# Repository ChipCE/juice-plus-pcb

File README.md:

# juice-plus-pcb
Varios PCB design for 3D printers and drones

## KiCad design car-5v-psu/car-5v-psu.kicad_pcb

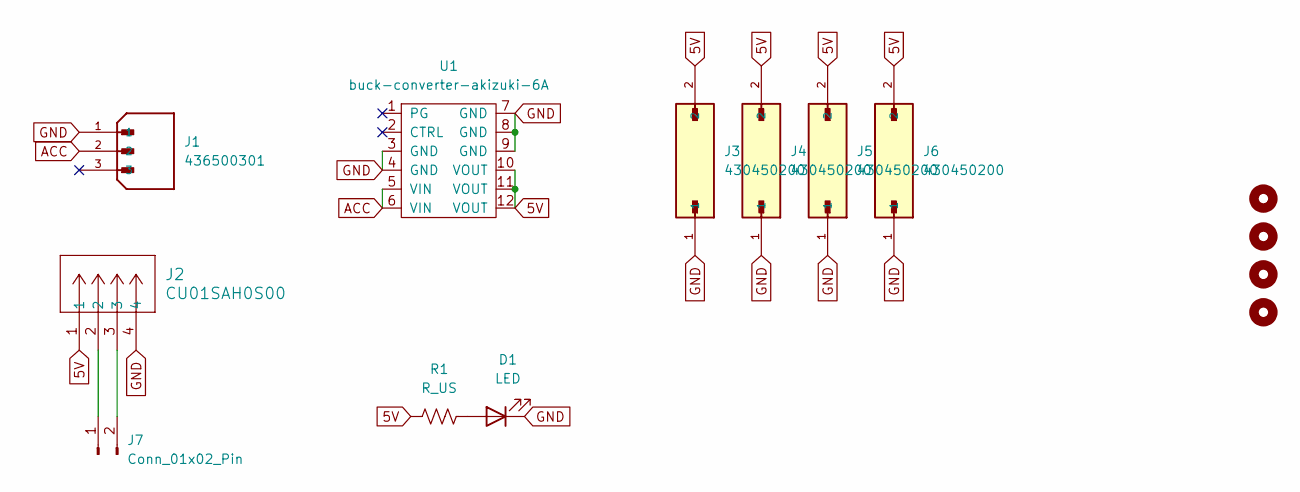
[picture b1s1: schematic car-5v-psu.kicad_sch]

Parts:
D1: LED; LED_0805_2012Metric
H1, H2, H3, H4: MountingHole; MountingHole_3.2mm_M3_ISO7380_Pad
J1: 436500301; MOLEX_436500301; PARTREV D7
J2: CU01SAH0S00; CONN_CU01SAH0S00_CVI
J3, J4, J5, J6: 430450200; MOLEX_430450200; PARTREV G
J7: Conn_01x02_Pin; PinHeader_1x02_P2.54mm_Vertical
R1: R_US; R_0805_2012Metric
U1: buck-converter-akizuki-6A

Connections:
5V: J2.1, J3.2, J4.2, J5.2, J6.2, R1.1, U1.10 (VOUT), U1.11 (VOUT), U1.12 (VOUT)
ACC: J1.2, U1.5 (VIN), U1.6 (VIN)
GND: D1.1 (K), J1.1, J2.4, J3.1, J4.1, J5.1, J6.1, U1.3 (GND), U1.4 (GND), U1.7 (GND), U1.8 (GND), U1.9 (GND)
unnamed: D1.2 (A), R1.2
unnamed: J2.2, J7.1
unnamed: J2.3, J7.2

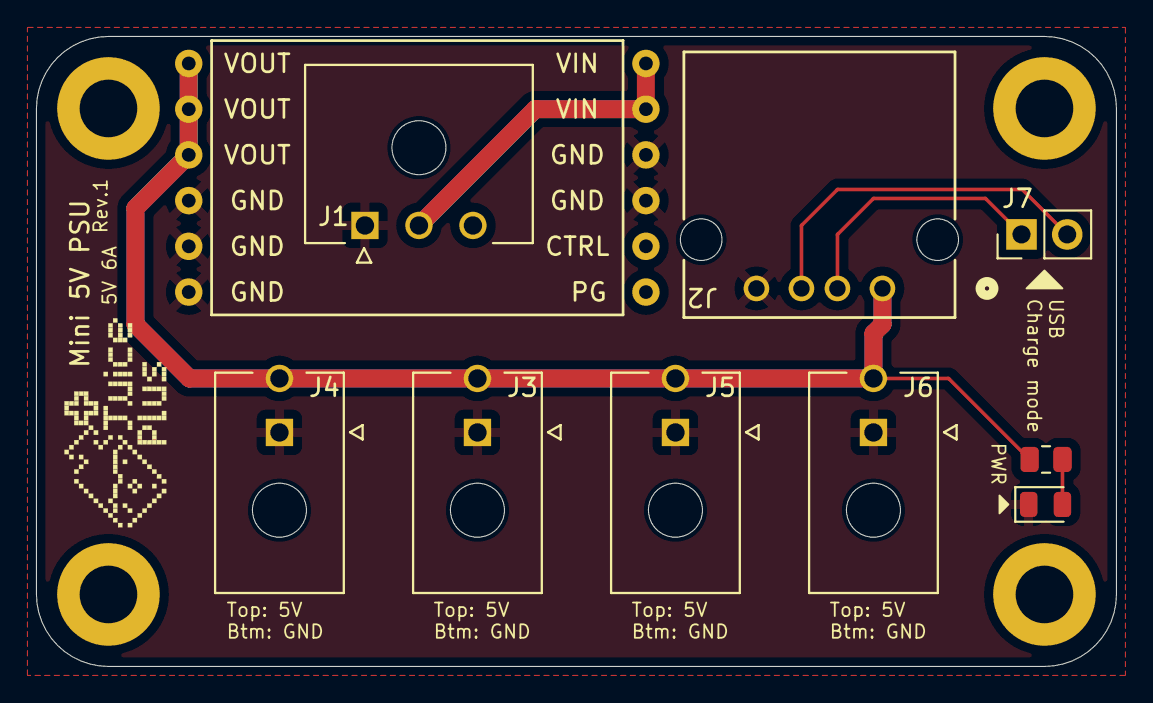
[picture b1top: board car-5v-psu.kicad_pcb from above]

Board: 2 copper layers, 60.0 x 35.0 mm, 14 parts (0 on the bottom side), 6 nets.

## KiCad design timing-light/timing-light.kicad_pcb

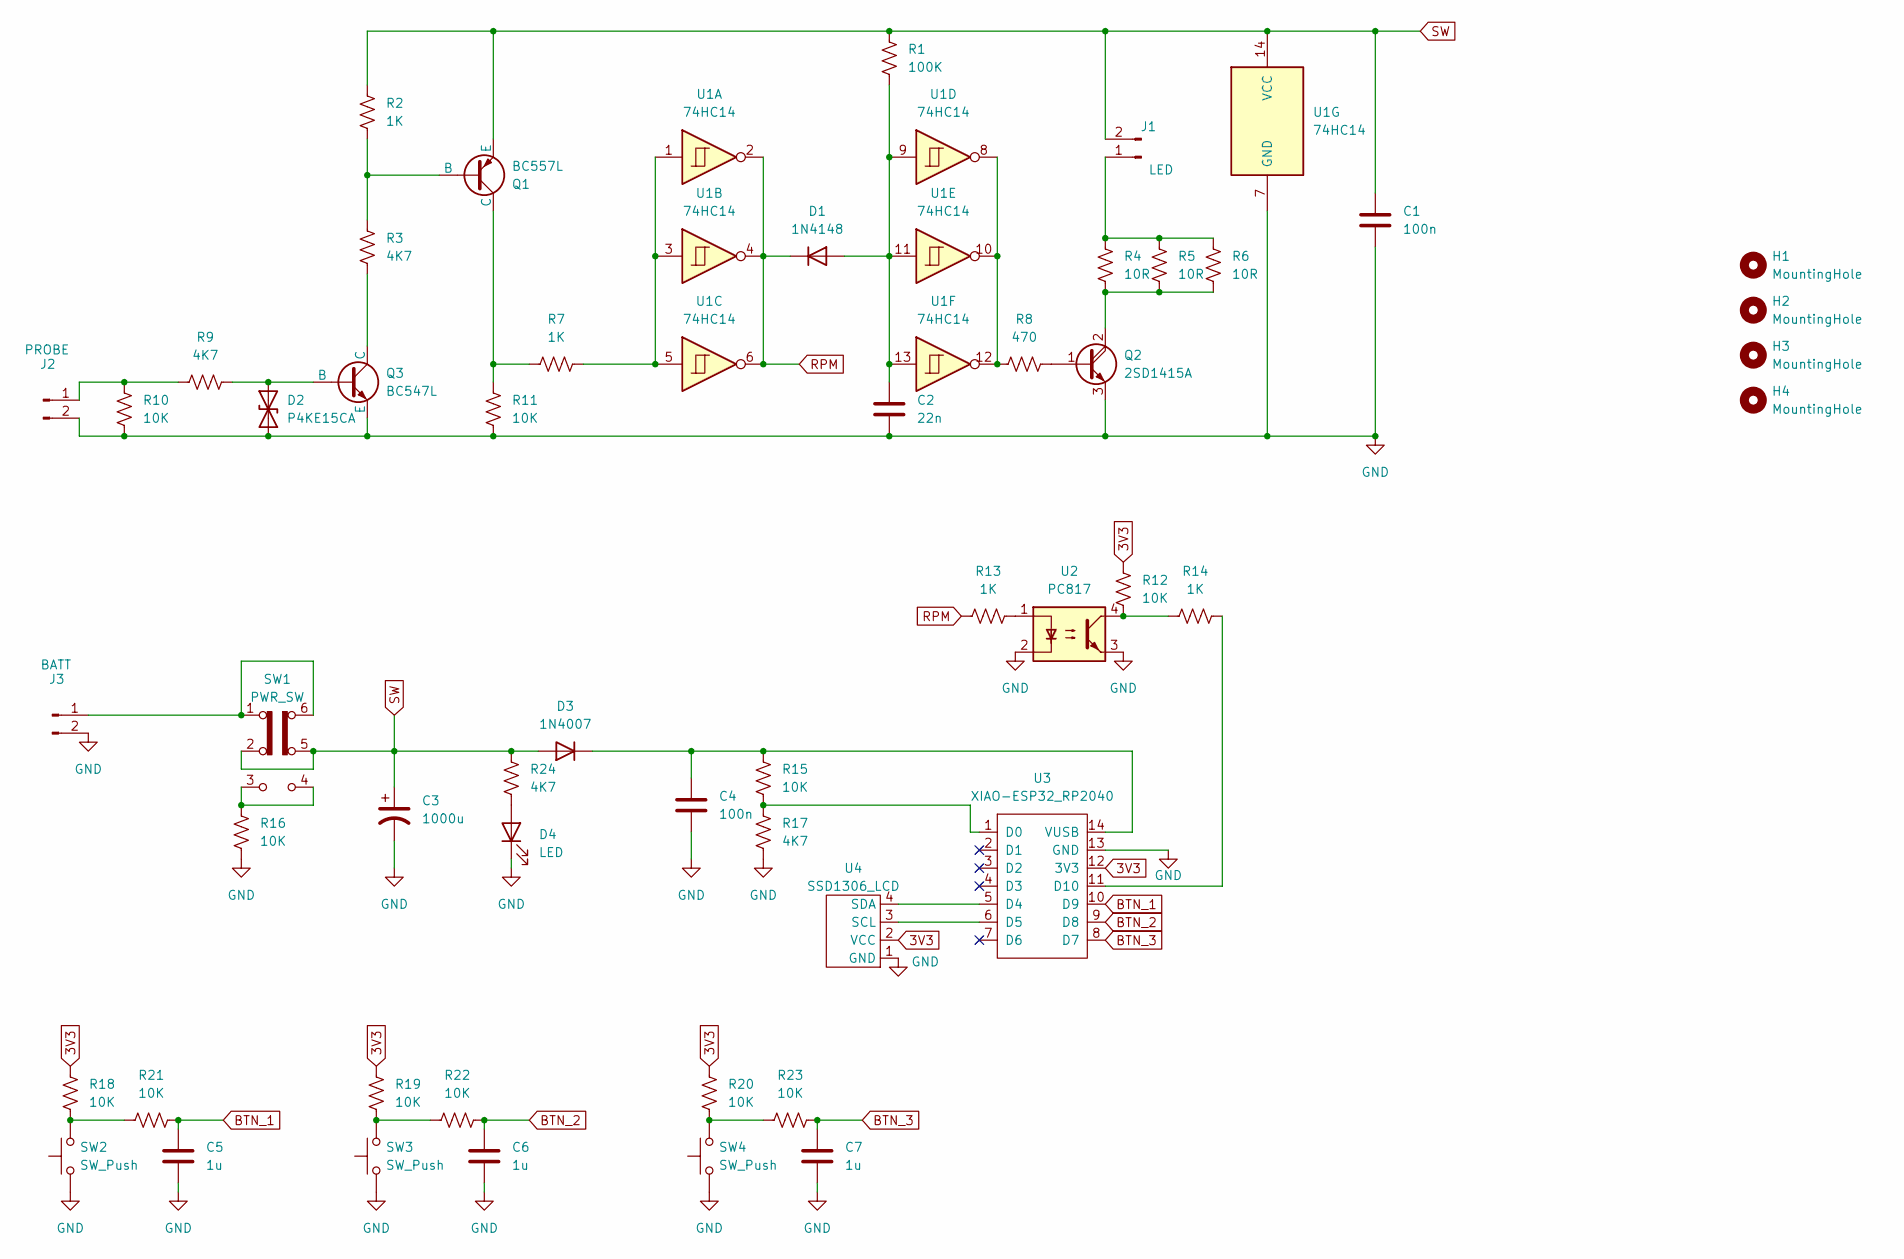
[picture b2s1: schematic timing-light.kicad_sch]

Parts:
C1, C4: 100n; C_Disc_D7.5mm_W4.4mm_P5.00mm
C2: 22n; C_Disc_D14.5mm_W5.0mm_P10.00mm
C3: 1000u; CP_Radial_D10.0mm_P5.00mm
C5, C6, C7: 1u; C_Disc_D7.5mm_W4.4mm_P5.00mm
D1: 1N4148; D_DO-35_SOD27_P7.62mm_Horizontal
D2: P4KE15CA; D_DO-41_SOD81_P10.16mm_Horizontal
D3: 1N4007; D_5W_P10.16mm_Horizontal
D4: LED; LED_D3.0mm_Horizontal_O1.27mm_Z2.0mm
H1, H2, H3, H4: MountingHole; MountingHole_3.2mm_M3_DIN965_Pad
J1: LED; JST_XH_B2B-XH-A_1x02_P2.50mm_Vertical
J2: PROBE; JST_XH_B2B-XH-A_1x02_P2.50mm_Vertical
J3: BATT; JST_XH_B2B-XH-A_1x02_P2.50mm_Vertical
Q1: BC557L; TO-92_Inline
Q2: 2SD1415A; TO-220-3_Horizontal_TabDown
Q3: BC547L; TO-92_Inline
R1: 100K; R_Axial_DIN0207_L6.3mm_D2.5mm_P10.16mm_Horizontal
R2, R7, R13, R14: 1K; R_Axial_DIN0207_L6.3mm_D2.5mm_P10.16mm_Horizontal
R3, R9, R17, R24: 4K7; R_Axial_DIN0207_L6.3mm_D2.5mm_P10.16mm_Horizontal
R4, R5, R6: 10R; R_Axial_DIN0309_L9.0mm_D3.2mm_P12.70mm_Horizontal
R8: 470; R_Axial_DIN0207_L6.3mm_D2.5mm_P10.16mm_Horizontal
R10, R11, R12, R15, R16, R18, R19, R20, R21, R22, R23: 10K; R_Axial_DIN0207_L6.3mm_D2.5mm_P10.16mm_Horizontal
SW1: PWR_SW; Switch_SS22F06G5
SW2, SW3, SW4: SW_Push; SW_PUSH_6mm
U1: 74HC14; DIP-14_W7.62mm_LongPads
U2: PC817; DIP-4_W7.62mm
U3: XIAO-ESP32_RP2040; XIAO_ESP32C_TH
U4: SSD1306_LCD; 0.96_inch_LCD_SSD1306

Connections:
3V3: R12.2, R18.2, R19.2, R20.2, U3.12 (3V3), U4.2 (VCC)
BTN_1: C5.1, R21.1, U3.10 (D9)
BTN_2: C6.1, R22.1, U3.9 (D8)
BTN_3: C7.1, R23.1, U3.8 (D7)
GND: C1.2, C2.2, C3.2, C4.2, C5.2, C6.2, C7.2, D2.1 (A1), D4.1 (K), J2.2, J3.2, Q2.3 (E), Q3.3 (E), R10.2, R11.1, R16.1, R17.1, SW2.1, SW3.1, SW4.1, U1.7 (GND), U2.2, U2.3, U3.13 (GND), U4.1 (GND)
unnamed: C2.1, D1.2 (A), R1.2, U1.9, U1.11, U1.13
unnamed: D2.2 (A2), Q3.2 (B), R9.2
unnamed: C4.1, D3.1 (K), R15.2, U3.14 (VUSB)
unnamed: D4.2 (A), R24.1
unnamed: J1.1, R4.2, R5.2, R6.2
unnamed: J2.1, R9.1, R10.1
unnamed: J3.1, SW1.1 (A), SW1.6 (C)
unnamed: Q1.2 (B), R2.2, R3.2
unnamed: Q1.1 (C), R7.1, R11.2
unnamed: Q2.1 (B), R8.2
unnamed: Q2.2 (C), R4.1, R5.1, R6.1
unnamed: Q3.1 (C), R3.1
unnamed: R7.2, U1.1, U1.3, U1.5
unnamed: R8.1, U1.8, U1.10, U1.12
unnamed: R12.1, R14.1, U2.4
unnamed: R13.2, U2.1
unnamed: R16.2, SW1.3 (C), SW1.4 (A)
unnamed: R18.1, R21.2, SW2.2
unnamed: R19.1, R22.2, SW3.2
unnamed: R20.1, R23.2, SW4.2
unnamed: R15.1, R17.2, U3.1 (D0)
unnamed: U3.5 (D4), U4.4 (SDA)
unnamed: U3.6 (D5), U4.3 (SCL)
unnamed: R14.2, U3.11 (D10)
RPM: D1.1 (K), R13.1, U1.2, U1.4, U1.6
SW: C1.1, C3.1, D3.2 (A), J1.2, Q1.3 (E), R1.1, R2.1, R24.2, SW1.2 (B), SW1.5 (B), U1.14 (VCC)

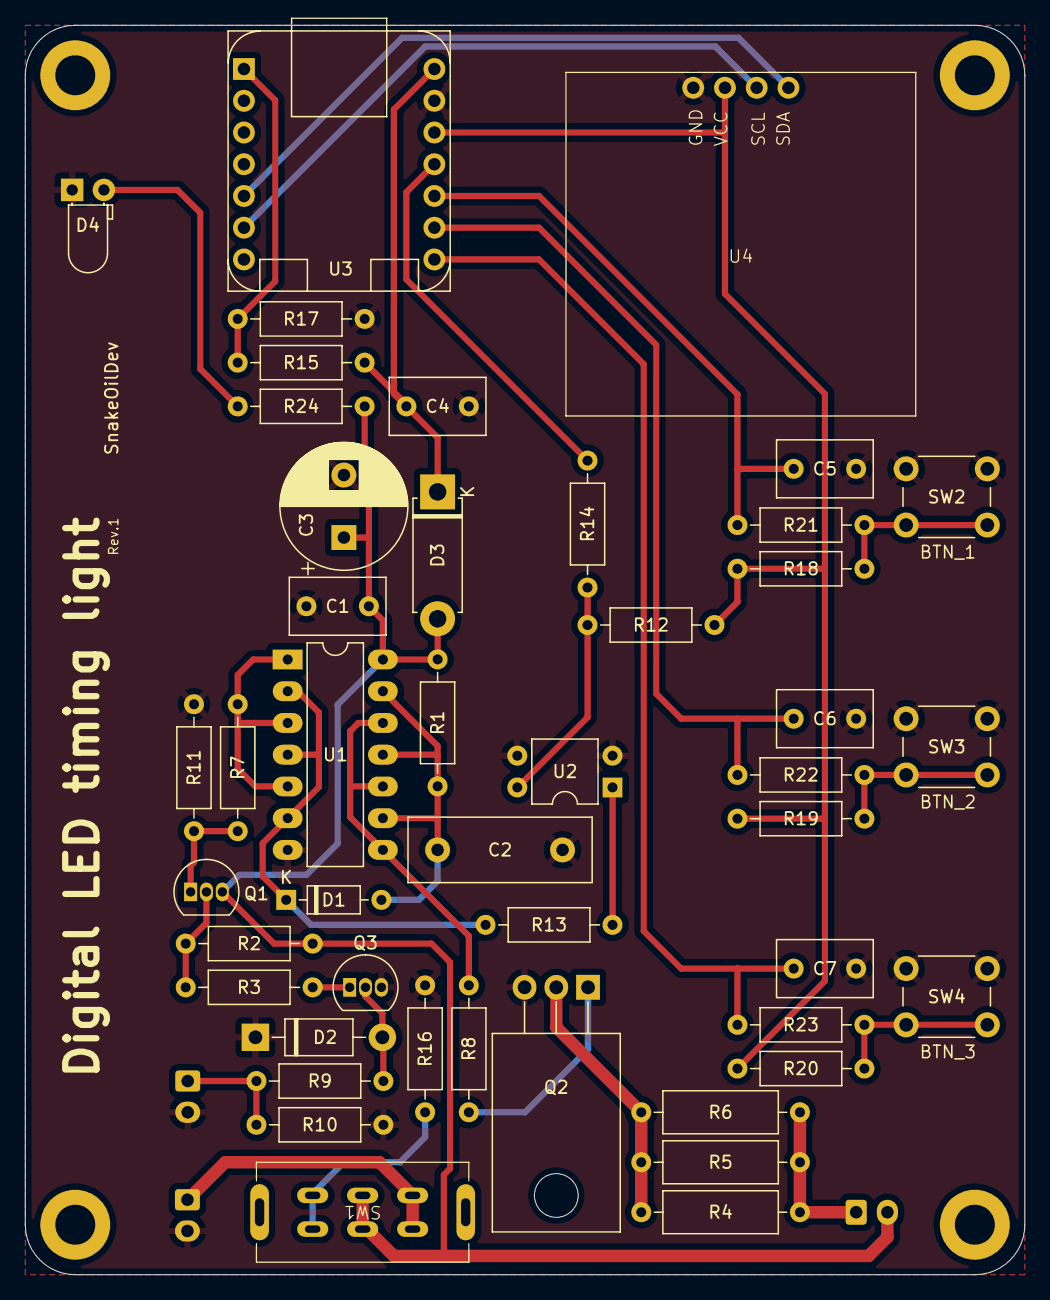
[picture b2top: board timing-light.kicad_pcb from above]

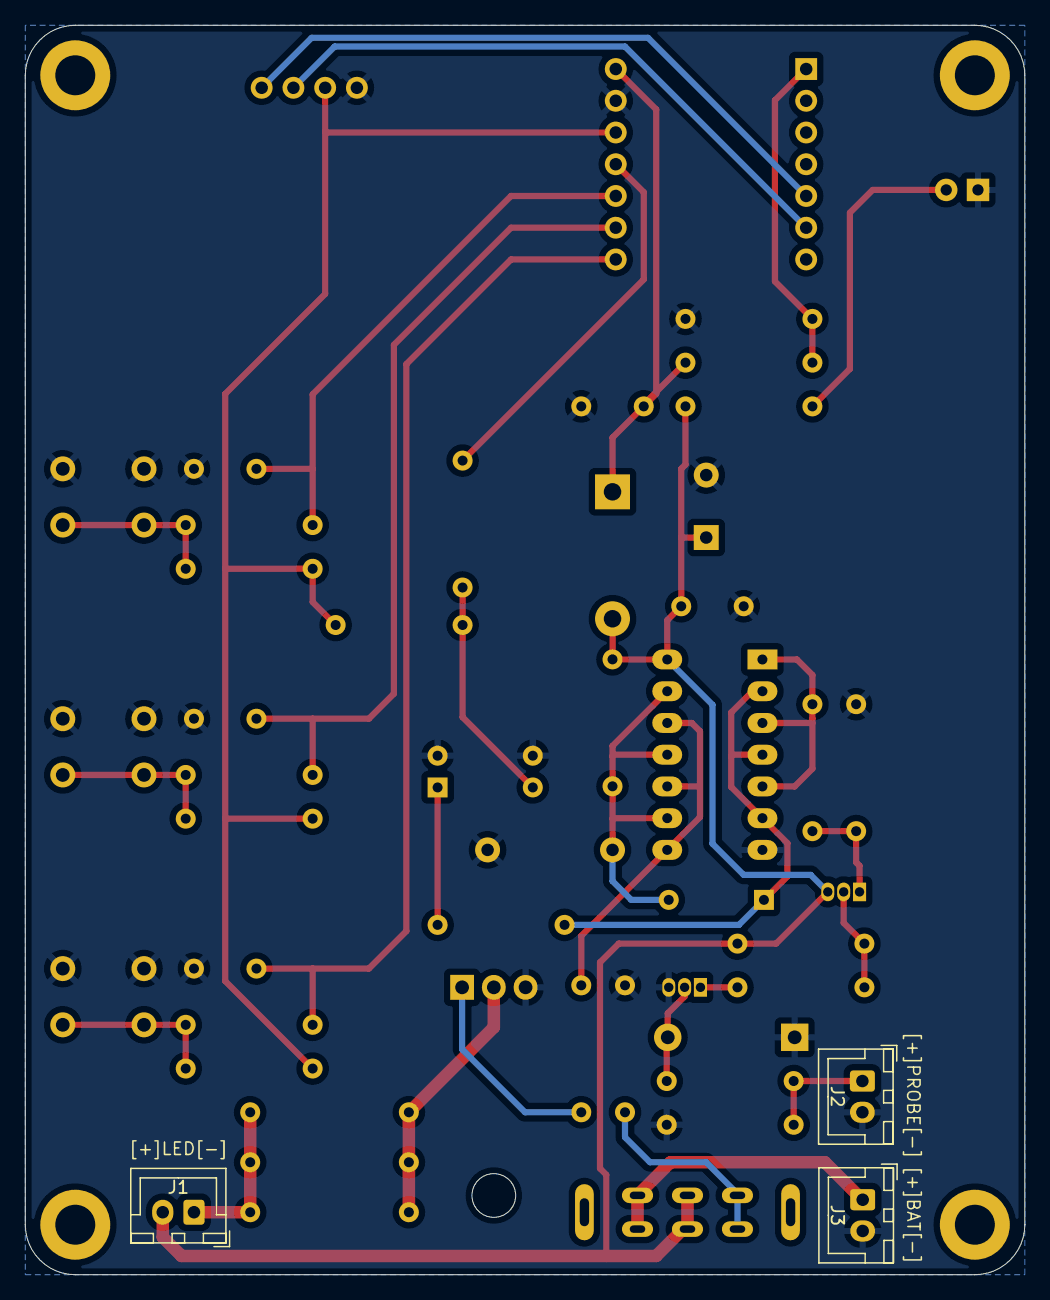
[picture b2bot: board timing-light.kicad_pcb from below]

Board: 2 copper layers, 80.0 x 100.0 mm, 53 parts (3 on the bottom side), 31 nets.

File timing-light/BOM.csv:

"Reference","Value","Datasheet","Footprint","Qty","DNP"
"C1,C4,C5,C6,C7","100n","~","Capacitor_THT:C_Disc_D7.5mm_W4.4mm_P5.00mm","5",""
"C2","22n","~","Capacitor_THT:C_Disc_D14.5mm_W5.0mm_P10.00mm","1",""
"C3","1000u","~","Capacitor_THT:CP_Radial_D10.0mm_P5.00mm","1",""
"D1","1N4148","https://assets.nexperia.com/documents/data-sheet/1N4148_1N4448.pdf","Diode_THT:D_DO-35_SOD27_P7.62mm_Horizontal","1",""
"D2","P4KE15CA","https://www.vishay.com/docs/88301/15ke.pdf","Diode_THT:D_DO-41_SOD81_P10.16mm_Horizontal","1",""
"D3","1N4007","https://assets.nexperia.com/documents/data-sheet/1N4148_1N4448.pdf","Diode_THT:D_5W_P10.16mm_Horizontal","1",""
"D4,J1","LED","~","-- mixed values --","2",""
"J2","PROBE","~","Connector_JST:JST_XH_B2B-XH-A_1x02_P2.50mm_Vertical","1",""
"J3","BATT","~","Connector_JST:JST_XH_B2B-XH-A_1x02_P2.50mm_Vertical","1",""
"Q1","BC557L","","Package_TO_SOT_THT:TO-92_Inline","1",""
"Q2","2SD1415A","","Package_TO_SOT_THT:TO-220-3_Horizontal_TabDown","1",""
"Q3","BC547L","","Package_TO_SOT_THT:TO-92_Inline","1",""
"R1","100K","~","Resistor_THT:R_Axial_DIN0207_L6.3mm_D2.5mm_P10.16mm_Horizontal","1",""
"R2,R7,R13,R14","1K","~","Resistor_THT:R_Axial_DIN0207_L6.3mm_D2.5mm_P10.16mm_Horizontal","4",""
"R3,R9,R17,R24","4K7","~","Resistor_THT:R_Axial_DIN0207_L6.3mm_D2.5mm_P10.16mm_Horizontal","4",""
"R4,R5,R6","10R","~","Resistor_THT:R_Axial_DIN0309_L9.0mm_D3.2mm_P12.70mm_Horizontal","3",""
"R8","470","~","Resistor_THT:R_Axial_DIN0207_L6.3mm_D2.5mm_P10.16mm_Horizontal","1",""
"R10,R11,R12,R15,R16,R18,R19,R20,R21,R22,R23","10K","~","Resistor_THT:R_Axial_DIN0207_L6.3mm_D2.5mm_P10.16mm_Horizontal","11",""
"SW1","PWR_SW","~","custom-footprints:Switch_SS22F06G5","1",""
"SW2,SW3,SW4","SW_Push","~","Button_Switch_THT:SW_PUSH_6mm","3",""
"U1","74HC14","http://www.ti.com/lit/gpn/sn74HC14","Package_DIP:DIP-14_W7.62mm_LongPads","1",""
"U2","TLP785","https://toshiba.semicon-storage.com/info/docget.jsp?did=1056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","Package_DIP:DIP-4_W7.62mm","1",""
"U3","XIAO-ESP32_RP2040","","custom-footprints:XIAO_ESP32C_TH","1",""
"U4","SSD1306_LCD","","custom-footprints:0.96_inch_LCD_SSD1306","1",""

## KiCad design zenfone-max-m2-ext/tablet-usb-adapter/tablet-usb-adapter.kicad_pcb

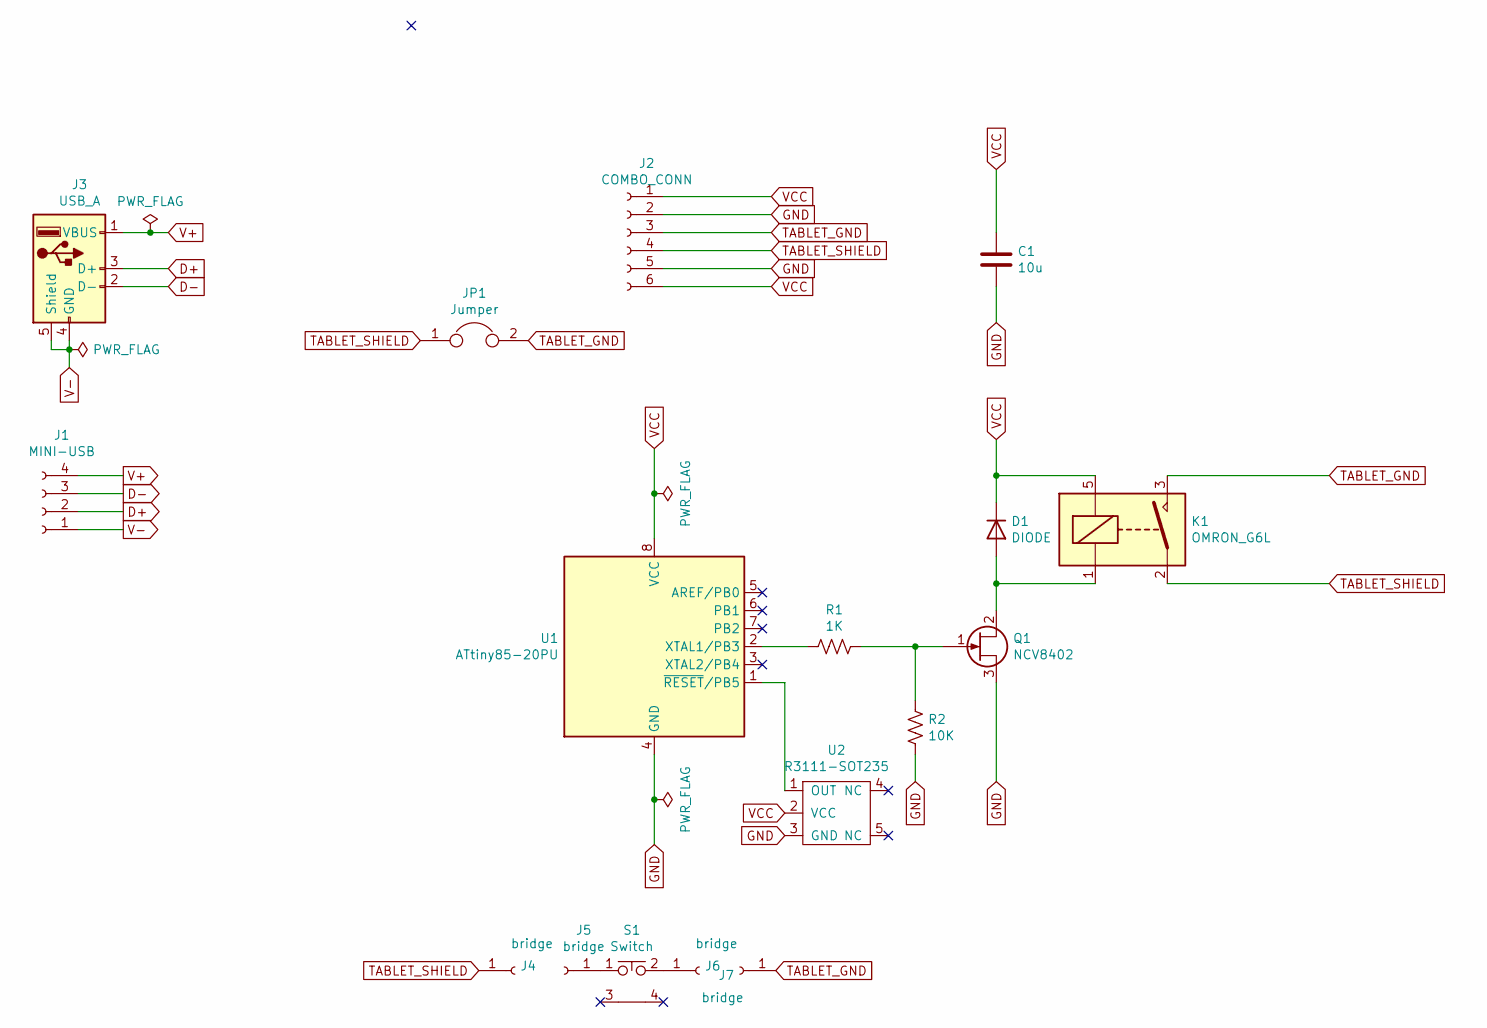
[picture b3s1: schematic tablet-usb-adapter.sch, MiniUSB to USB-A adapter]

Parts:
C1: 10u; C_0805_2012Metric_Pad1.18x1.45mm_HandSolder
D1: DIODE; D_SOD-123
J1: MINI-USB; PinHeader_1x04_P2.54mm_Vertical
J2: COMBO_CONN; JST_XH_S6B-XH-A_1x06_P2.50mm_Horizontal
J3: USB_A; USB_A_CONNFLY_DS1095-WNR0
J4, J5, J6, J7: bridge; PinSocket_1x01_P1.27mm_Vertical
JP1: Jumper; SolderJumper-2_P1.3mm_Open_RoundedPad1.0x1.5mm
K1: OMRON_G6L; RELAY_OMRON_G6L
Q1: NCV8402; SOT-223-3_TabPin2
R1: 1K; R_0805_2012Metric_Pad1.20x1.40mm_HandSolder
R2: 10K; R_0805_2012Metric_Pad1.20x1.40mm_HandSolder
S1: Switch; switch-side-btn
U1: ATtiny85-20PU; DIP-8_W7.62mm
U2: R3111-SOT235; SOT-23-5

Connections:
D+: J1.2, J3.3 (D+)
D-: J1.3, J3.2 (D-)
GND: C1.2, J2.2, J2.5, Q1.3 (S), R2.2, U1.4 (GND), U2.3 (GND)
unnamed: D1.1 (A), K1.1, Q1.2 (D)
unnamed: J5.1, S1.1
unnamed: J6.1, S1.2
unnamed: Q1.1 (G), R1.1, R2.1
unnamed: R1.2, U1.2 (XTAL1/PB3)
unnamed: U1.1 (~RESET~/PB5), U2.1 (OUT)
TABLET_GND: J2.3, J7.1, JP1.2, K1.3
TABLET_SHIELD: J2.4, J4.1, JP1.1, K1.2
V+: J1.4, J3.1 (VBUS)
V-: J1.1, J3.4 (GND), J3.5 (Shield)
VCC: C1.1, D1.2 (K), J2.1, J2.6, K1.5, U1.8 (VCC), U2.2 (VCC)

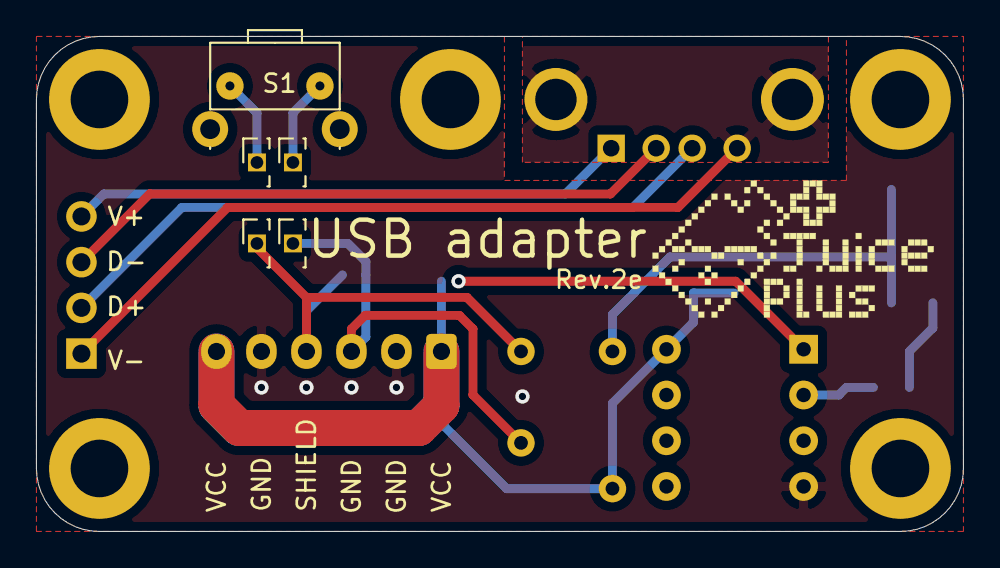
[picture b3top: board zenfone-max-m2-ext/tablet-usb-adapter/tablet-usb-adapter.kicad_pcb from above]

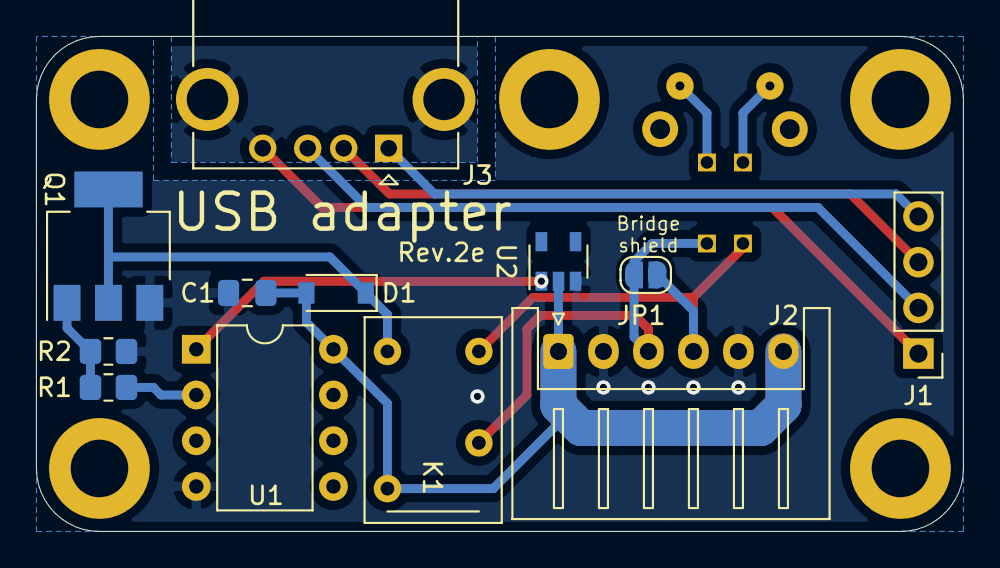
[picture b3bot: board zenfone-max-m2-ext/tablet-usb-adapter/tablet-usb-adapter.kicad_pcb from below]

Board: 2 copper layers, 51.5 x 27.5 mm, 17 parts (12 on the bottom side), 14 nets.

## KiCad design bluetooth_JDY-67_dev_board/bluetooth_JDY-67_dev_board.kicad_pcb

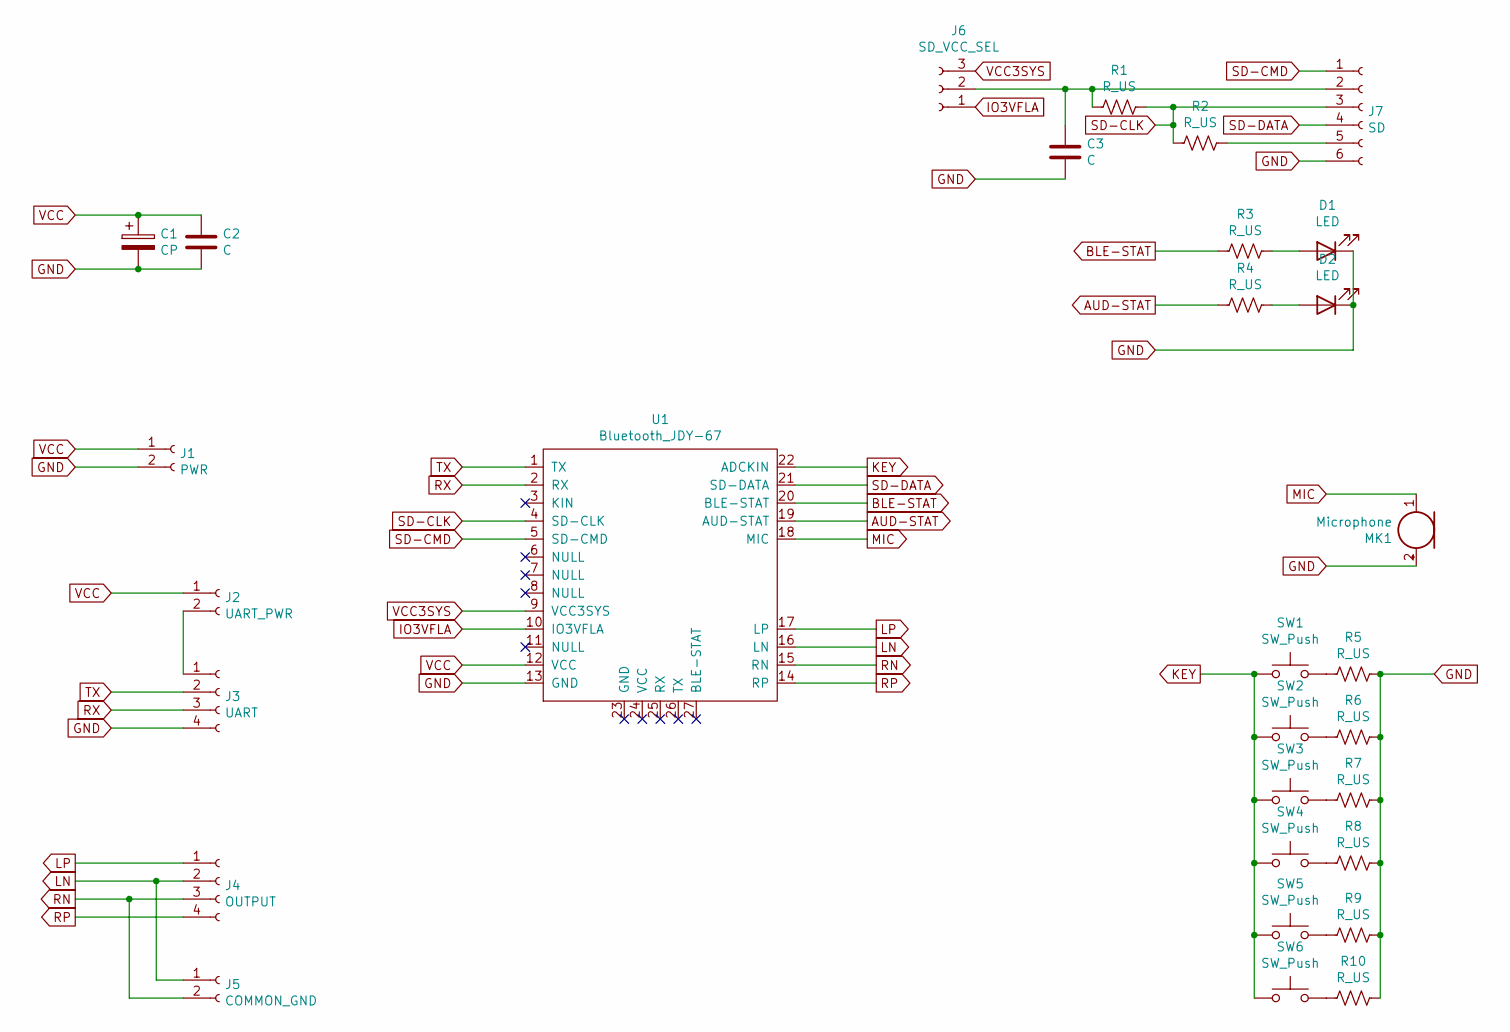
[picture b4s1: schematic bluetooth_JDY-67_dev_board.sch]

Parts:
C1: CP; CP_Radial_D5.0mm_P2.00mm
C2, C3: C; R_0805_2012Metric_Pad1.20x1.40mm_HandSolder
D1, D2: LED; LED_0805_2012Metric_Pad1.15x1.40mm_HandSolder
J1: PWR; JST_XH_B2B-XH-A_1x02_P2.50mm_Vertical
J2: UART_PWR; PinHeader_1x02_P2.54mm_Vertical
J3: UART; JST_XH_B4B-XH-A_1x04_P2.50mm_Vertical
J4: OUTPUT; JST_XH_B4B-XH-A_1x04_P2.50mm_Vertical
J5: COMMON_GND; PinHeader_1x02_P2.54mm_Vertical
J6: SD_VCC_SEL; PinHeader_1x03_P2.54mm_Vertical
J7: SD; JST_XH_B6B-XH-A_1x06_P2.50mm_Vertical
MK1: Microphone; CP_Radial_D10.0mm_P2.50mm
R1, R2, R3, R4, R5, R6, R7, R8, R9, R10: R_US; R_0805_2012Metric_Pad1.20x1.40mm_HandSolder
SW1, SW2, SW3, SW4, SW5, SW6: SW_Push; SW_PUSH_6mm
U1: Bluetooth_JDY-67

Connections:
AUD-STAT: R4.2, U1.19 (AUD-STAT)
BLE-STAT: R3.2, U1.20 (BLE-STAT)
GND: C1.2, C2.2, C3.2, D1.1 (K), D2.1 (K), J1.2, J3.4, J7.6, MK1.2 (+), R5.1, R6.1, R7.1, R8.1, R9.1, R10.1, U1.13 (GND)
IO3VFLA: J6.1, U1.10 (IO3VFLA)
KEY: SW1.1, SW2.1, SW3.1, SW4.1, SW5.1, SW6.1, U1.22 (ADCKIN)
LN: J4.2, J5.1, U1.16 (LN)
LP: J4.1, U1.17 (LP)
MIC: MK1.1 (-), U1.18 (MIC)
unnamed: C3.1, J6.2, J7.2, R1.2
unnamed: D1.2 (A), R3.1
unnamed: D2.2 (A), R4.1
unnamed: J2.2, J3.1
unnamed: J7.5, R2.1
unnamed: R5.2, SW1.2
unnamed: R6.2, SW2.2
unnamed: R7.2, SW3.2
unnamed: R8.2, SW4.2
unnamed: R9.2, SW5.2
unnamed: R10.2, SW6.2
RN: J4.3, J5.2, U1.15 (RN)
RP: J4.4, U1.14 (RP)
RX: J3.3, U1.2 (RX)
SD-CLK: J7.3, R1.1, R2.2, U1.4 (SD-CLK)
SD-CMD: J7.1, U1.5 (SD-CMD)
SD-DATA: J7.4, U1.21 (SD-DATA)
TX: J3.2, U1.1 (TX)
VCC: C1.1, C2.1, J1.1, J2.1, U1.12 (VCC)
VCC3SYS: J6.3, U1.9 (VCC3SYS)

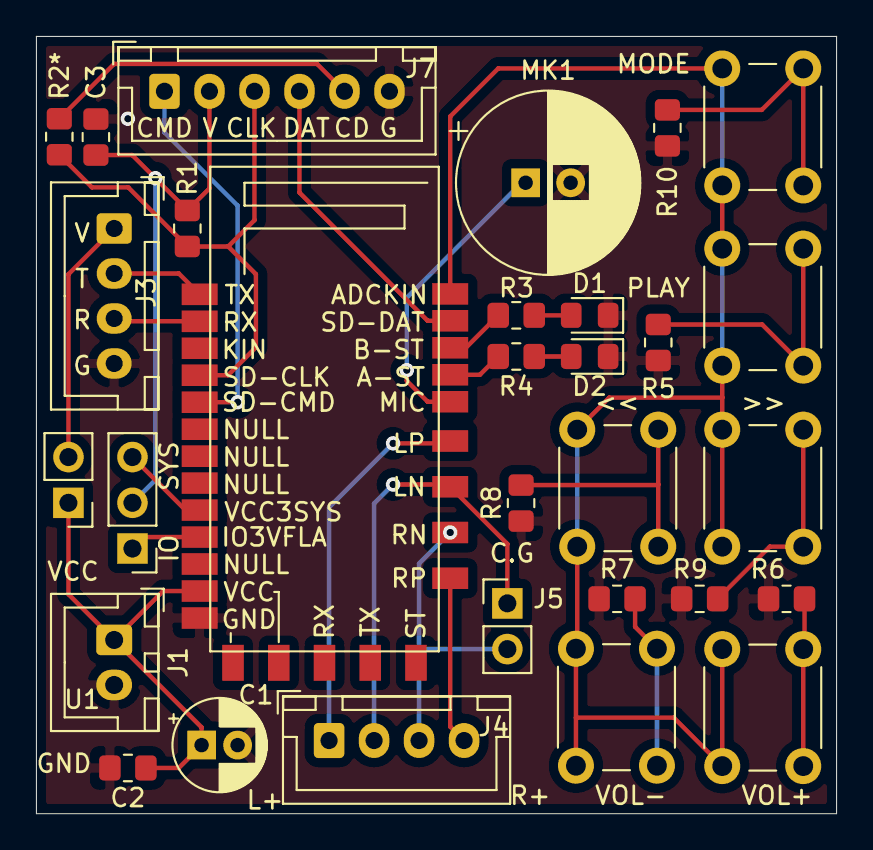
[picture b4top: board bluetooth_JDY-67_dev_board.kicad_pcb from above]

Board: 2 copper layers, 44.5 x 43.2 mm, 30 parts (0 on the bottom side), 28 nets.

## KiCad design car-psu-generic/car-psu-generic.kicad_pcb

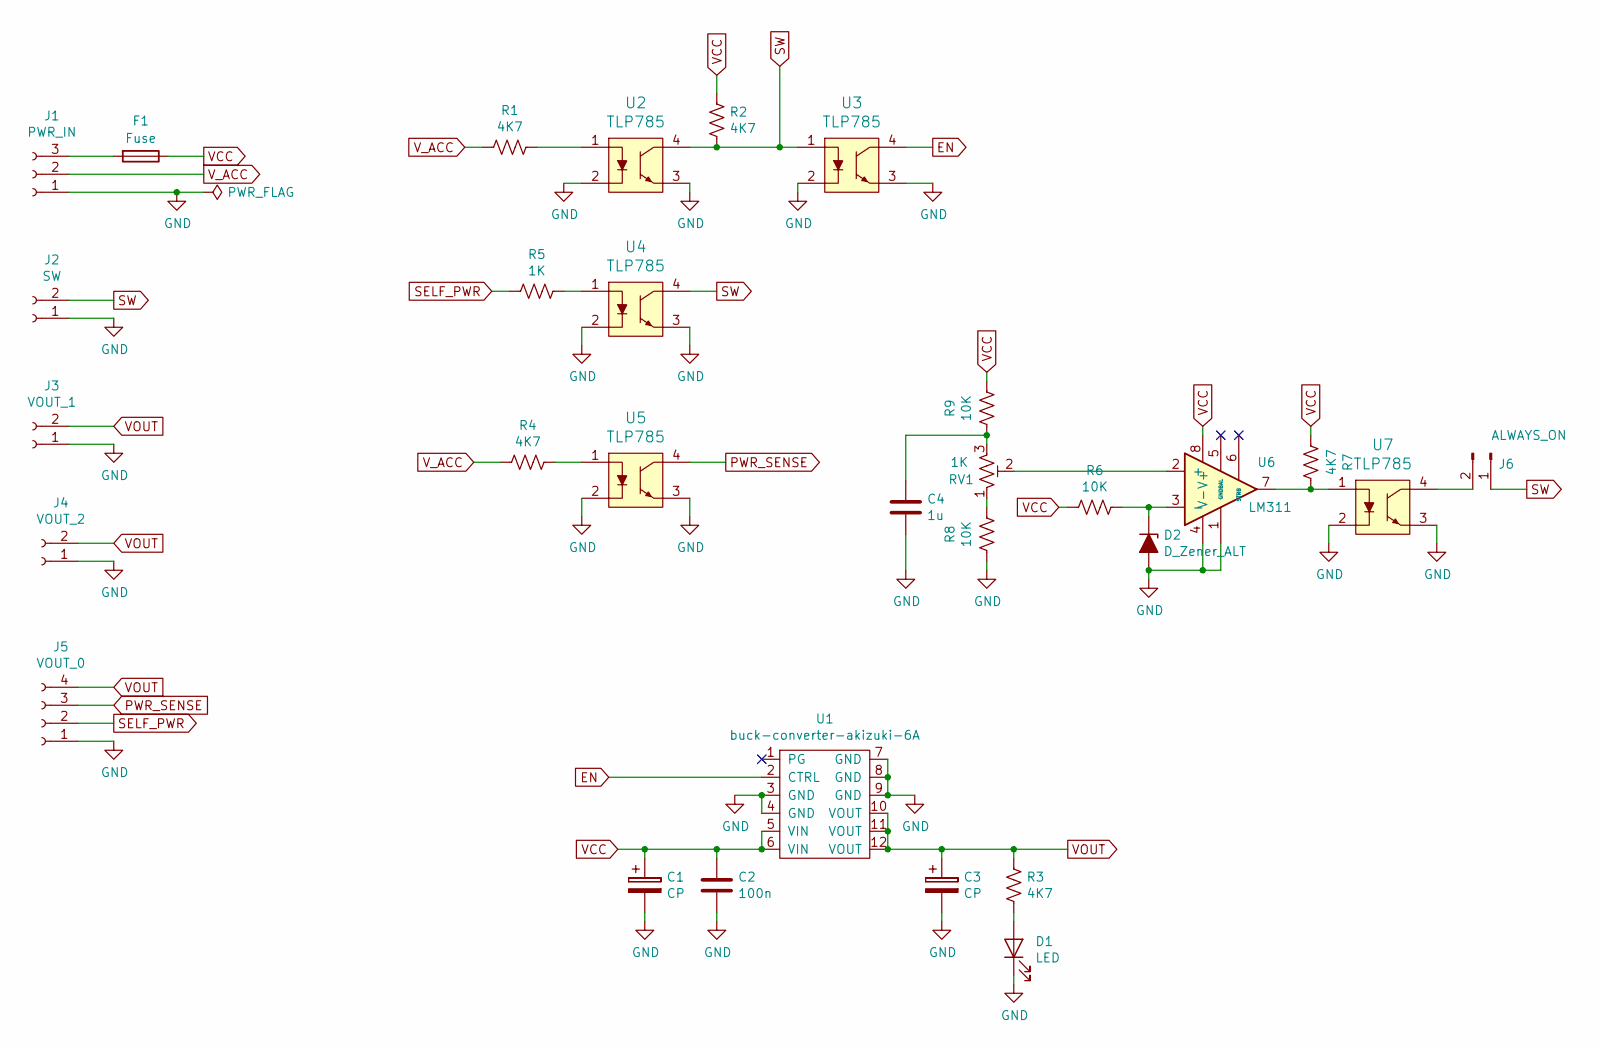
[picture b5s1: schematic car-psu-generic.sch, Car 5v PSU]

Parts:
C1, C3: CP; CP_Radial_D10.0mm_P5.00mm
C2: 100n; C_0805_2012Metric_Pad1.15x1.40mm_HandSolder
C4: 1u; C_0805_2012Metric_Pad1.15x1.40mm_HandSolder
D1: LED; LED_0805_2012Metric_Pad1.15x1.40mm_HandSolder
D2: D_Zener_ALT; D_SOD-123
F1: Fuse; Fuse_2920_7451Metric_Pad2.10x5.45mm_HandSolder
J1: PWR_IN; JST_XH_S03B-XH-A_1x03_P2.50mm_Horizontal
J2: SW; JST_XH_S02B-XH-A_1x02_P2.50mm_Horizontal
J3: VOUT_1; JST_XH_S02B-XH-A_1x02_P2.50mm_Horizontal
J4: VOUT_2; JST_XH_S02B-XH-A_1x02_P2.50mm_Horizontal
J5: VOUT_0; JST_XH_S04B-XH-A_1x04_P2.50mm_Horizontal
J6: ALWAYS_ON; PinHeader_1x02_P2.54mm_Vertical
R1, R2, R3, R4, R7: 4K7; R_0805_2012Metric_Pad1.15x1.40mm_HandSolder
R5: 1K; R_0805_2012Metric_Pad1.15x1.40mm_HandSolder
R6, R8, R9: 10K; R_0805_2012Metric_Pad1.15x1.40mm_HandSolder
RV1: 1K; Potentiometer_Vishay_T73YP_Vertical
U1: buck-converter-akizuki-6A
U2, U3, U4, U5, U7: TLP785; DIP-4_W7.62mm
U6: LM311; DIP-8_W7.62mm

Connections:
EN: U1.2 (CTRL), U3.4
GND: C1.2, C2.2, C3.2, C4.2, D1.1 (K), D2.2 (A), J1.1, J2.1, J3.1, J4.1, J5.1, R8.2, U1.3 (GND), U1.4 (GND), U1.7 (GND), U1.8 (GND), U1.9 (GND), U2.2, U2.3, U3.2, U3.3, U4.2, U4.3, U5.2, U5.3, U6.1 (GND), U6.4 (V-), U7.2, U7.3
unnamed: C4.1, R9.2, RV1.3
unnamed: D1.2 (A), R3.1
unnamed: D2.1 (K), R6.1, U6.3 (-)
unnamed: F1.2, J1.3
unnamed: J6.2, U7.4
unnamed: R1.1, U2.1
unnamed: R4.1, U5.1
unnamed: R5.1, U4.1
unnamed: R7.1, U6.7, U7.1
unnamed: R8.1, RV1.1
unnamed: RV1.2, U6.2 (+)
PWR_SENSE: J5.3, U5.4
SELF_PWR: J5.2, R5.2
SW: J2.2, J6.1, R2.2, U2.4, U3.1, U4.4
VCC: C1.1, C2.1, F1.1, R2.1, R6.2, R7.2, R9.1, U1.5 (VIN), U1.6 (VIN), U6.8 (V+)
VOUT: C3.1, J3.2, J4.2, J5.4, R3.2, U1.10 (VOUT), U1.11 (VOUT), U1.12 (VOUT)
V_ACC: J1.2, R1.2, R4.2

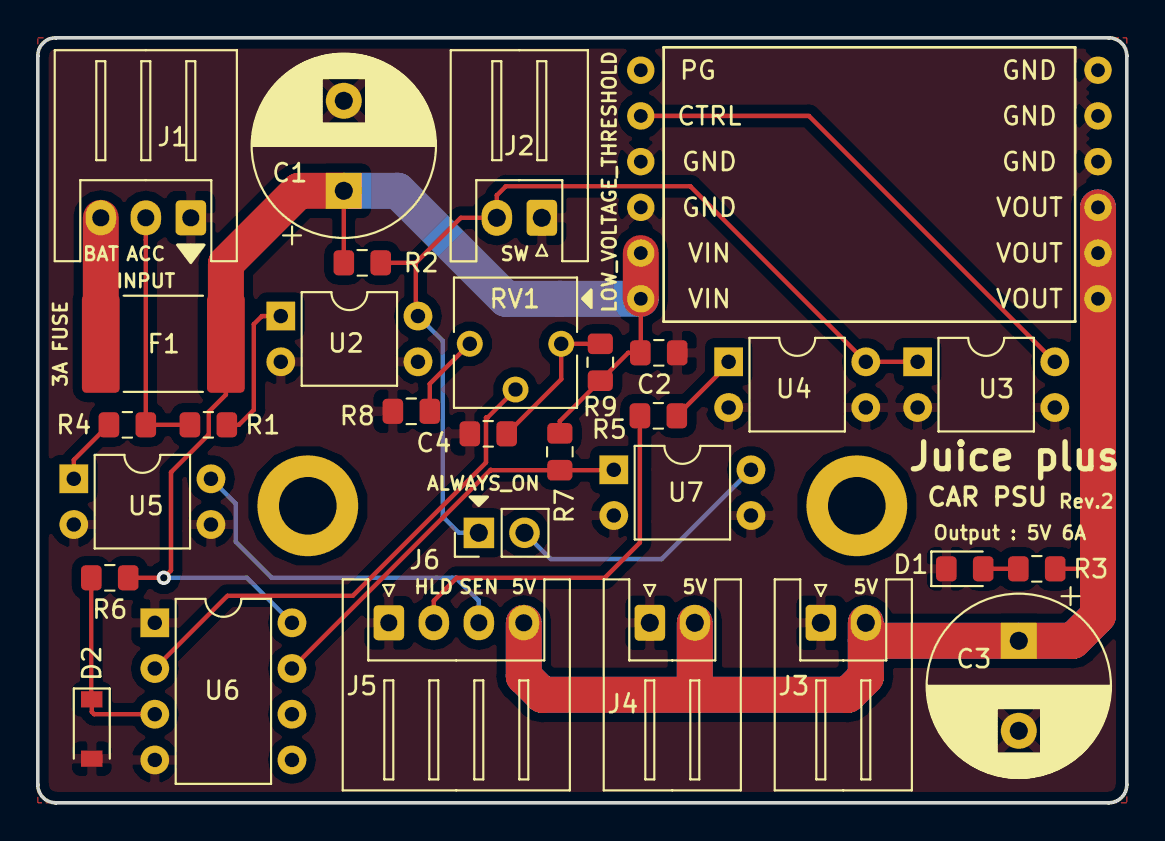
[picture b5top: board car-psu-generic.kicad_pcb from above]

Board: 2 copper layers, 60.5 x 42.5 mm, 30 parts (0 on the bottom side), 19 nets.

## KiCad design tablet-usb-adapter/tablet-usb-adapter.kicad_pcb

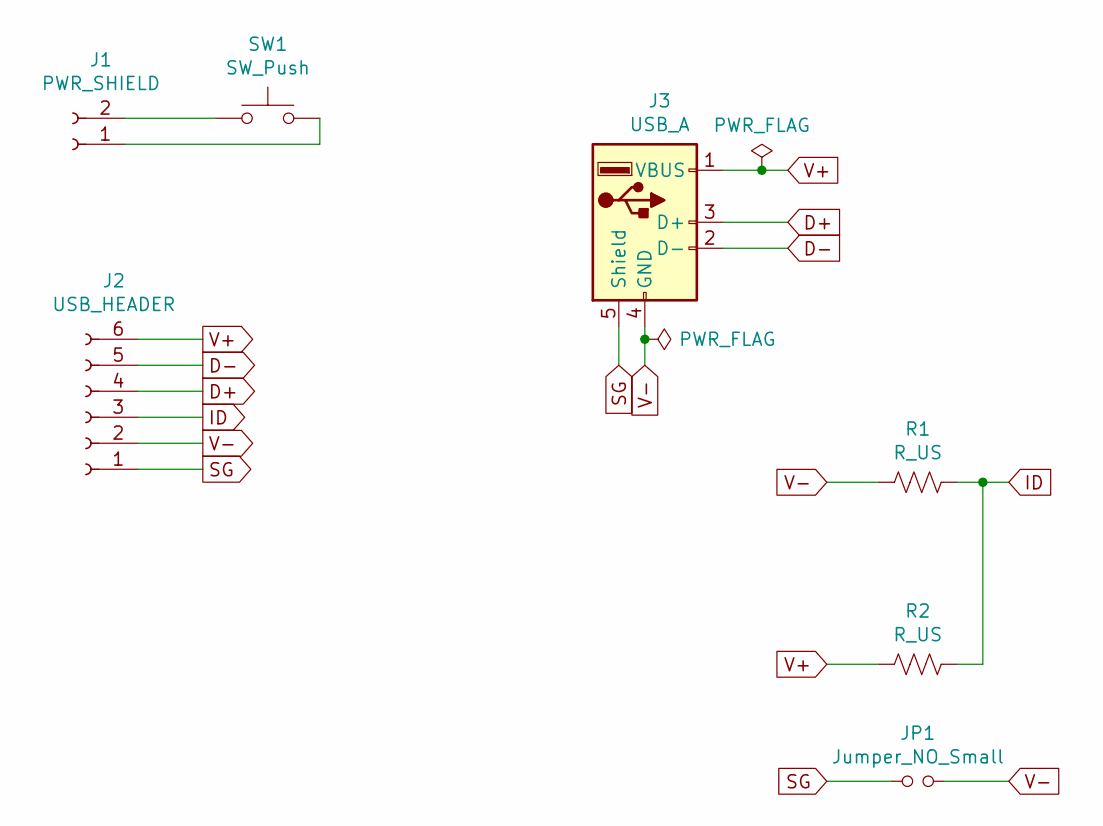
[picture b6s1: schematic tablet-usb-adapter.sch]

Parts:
J1: PWR_SHIELD; PinHeader_1x02_P2.54mm_Vertical
J2: USB_HEADER; PinHeader_1x06_P2.54mm_Vertical
J3: USB_A; USB_A_CONNFLY_DS1095-WNR0
JP1: Jumper_NO_Small; SolderJumper-2_P1.3mm_Open_RoundedPad1.0x1.5mm
R1, R2: R_US; R_0805_2012Metric_Pad1.20x1.40mm_HandSolder
SW1: SW_Push; SW_Tactile_SPST_Angled_PTS645Vx39-2LFS

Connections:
D+: J2.4, J3.3 (D+)
D-: J2.5, J3.2 (D-)
ID: J2.3, R1.1, R2.1
unnamed: J1.1, SW1.2
unnamed: J1.2, SW1.1
SG: J2.1, J3.5 (Shield), JP1.1
V+: J2.6, J3.1 (VBUS), R2.2
V-: J2.2, J3.4 (GND), JP1.2, R1.2

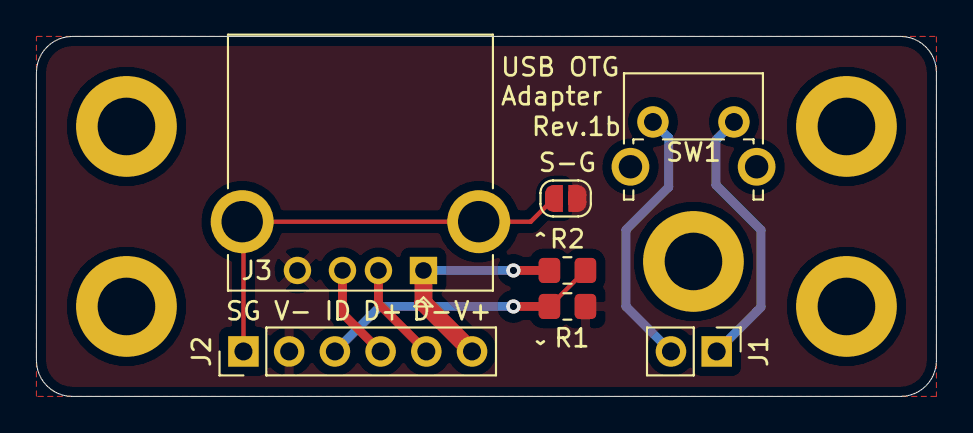
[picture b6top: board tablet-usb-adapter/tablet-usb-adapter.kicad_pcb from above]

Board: 2 copper layers, 50.0 x 20.0 mm, 7 parts (0 on the bottom side), 8 nets.
